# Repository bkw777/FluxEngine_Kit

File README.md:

# FluxEngine Kit

THESE PCBs ARE NOT TESTED YET

This is a set of adapter PCBs and printable snap covers to build a nice version of [FluxEngine](http://cowlark.com/fluxengine/)

I am not the creator of FluxEngine itself, just this adapter PCB and printable cover.

Most people probably do not need any of these pcbs. They are really just to provide convenient support for 8-inch drives.

If you're not trying to use 8-inch drives, then you don't need any adapter pcb like this.  
The FluxEngine pinout is already designed so that you can just solder a 34-pin connector directly to the CY8CKIT-059 fpga board.  
You can use the BOM link below and delete everything but the CY8CKIT-059 and the 34-pin connector, no pcb, no printed cover.

The PCBs are designed to NOT need to be soldered. You can connect and remove and reconnect the fpga board without, and without needing to install actual sockets.
You CAN still solder them normally if you want to make a permanent FluxEngine, you just don't have to.

It means you can swap the same fpga board between all 3 (so far) hat versions, and then still also use the fpga board on a breadboard when not using it for FluxEngine.

What you do is solder pins to the bottom of the fpga board the same as if you were using it on a breadboard. And that's it. You can install actual matching sockets on the hat PCBs, but you don't have to. The zig/zag pin row layout on the hat PCBs makes solid electrical contact with the pins without needing a socket.

For the sake of the solderless pin connections, I suggest getting the PCBs made with ENIG finish (gold plating on the copper).  
It's not required though. Honestly the way the square edges of the pins bite into the via walls it probably will never make any difference.  
Some fabricators charge more than others for ENIG. OSHPark is always ENIG no matter what, so that's easy. But between PCBWAY, JLCPCB, and Elecrow, Elecrow charges a lot less for ENIG.

The cover (both styles) prints easily with any basic home FDM printer with PLA. I actually use a $150 Monoprice from 6 years ago.  

But also these days most of the PCB shops also offer 3d printing, so you can get the pcb and the cover printed professionally in sintered nylon from the same place on the same order.  
The link below is to PCBWAY only because it's the most convenient where you can just click "buy" on something already pre-loaded, but actually if you go to Elecrow and just upload the gerber zip and cover stl, it's just as simple and significantly cheaper, especially with ENIG.

## Parts
[BOM from DigiKey](https://www.digikey.com/short/q5zh79n9)  
[PCB and Cover from PCBWAY](https://www.pcbway.com/project/shareproject/FluxEngine_Hat_e3000eb5.html)

Power supply and cables:  
[Molex power supply](https://amazon.com/dp/B000MGG6SC)  
[Molex to Berg splitter](https://amazon.com/dp/B0002J1KW6)  
[Molex to Molex splitter](https://amazon.com/dp/B00007JO36)  
[Floppy drive cable](https://amazon.com/dp/B07KDJTMGP)  

## Cover

There are a few versions of printable cover in releases, all generated from the same OpenSCAD source.  
Two main styles, simple and fancy, in three sizes each, lowprofile, default, and one for if you have full pin sockets installed.  

## Configuration

The jumpers only affect the 50-pin connector for 8-inch drives.  

### DSKCHG / READY
Connects either the /DSKCHG or /READY output from the drive to the /DSKCHG input on the FluxEngine.  

Install jumper on DSKCHG by default.

### INUSE
Connects the /MOTB (motor-B-on) output from the FluxEngine to the /IN-USE aka /DOOR-LOCK input on the drive.

Not connected by default, but stow a jumper on one pin.

### HLD
Connects the /MOTB (motor-B-on) output from the FluxEngine to the /HEAD-LOAD input on the drive.

Not connected by default, but stow a jumper on one pin.

INUSE/HLD is not either-or. You may need either, or neither, or both.

# Control Data / Magnetic Peripherals / Honeywell 8-inch drives

Some CDC 8-inch drives like the 9404 and 9406-4 lines are Shugart compatible, and so for those just use the SA850 hat like any other Shugart interface drive.

Others have compatible signals but different pinouts.

The two tables below come from two CDC manuals covering many similar drive models spanning several years.  
Left: [CDC FDD FSM ('79)](PCB/datasheets/CDC_77834769_Y__FDD_FSM.pdf)  
Right: [CDC 9406 FSM ('82)](PCB/datasheets/CDC_77614903_AM__9406_FSM.pdf)  

There are two hats that cover the most common CDC pinouts.

The "CDC-daisychain" hat supports all the green highlighted models.

The "CDC-standard" hat supports the blue and purple highlighted models.

"standard" is mis-named because what CDC called "standard interface" in the manuals was several different pinouts and interfaces.  
But of the several pinouts they called "standard", 2 are actually the same except for STEP+DIRECTION vs STEP_IN/STEP_OUT, and most models that don't have the "daisychain" interface seem to have one of these two versions of "standard".  
So the '''CDC-standard''' hat includes logic to optionally convert the STEP+DIRECTION signals from the FluxEngine to STEP_IN/STEP_OUT signals for the drive if needed.

For drives that need STEP_IN/STEP_OUT, install the 2 jumpers on STEP_IN and STEP_OUT. (earlier and less common drives)  

For drives that need STEP+DIRECTION, install the 2 jumpers on DIR and STEP. (default, later and more common drives)  

If you don't need the STEP_IN/STEP_OUT option, you don't need to populate C1 or U1 or the jumper pins. Just use solder or wire in place of the STEP & DIR jumpers and leave the U1 and C1 footprints empty.  

NONE OF THESE ARE TESTED YET  

CDC-daisychain BOM:  
Standard BOM, delete the jumpers.  

CDC-standard BOM:  
Standard BOM, add these:  
[screw terminal header](https://www.digikey.com/en/products/detail/phoenix-contact/5452094/5186805)  
[screw terminal plug](https://www.digikey.com/en/products/detail/phoenix-contact/5452178/5187210)  
[74LVC1G19 1to2 decoder](https://www.digikey.com/en/products/detail/nexperia-usa-inc/74LVC1G19GW-125/1231453)  
[C 0.1u 0805](https://www.digikey.com/en/products/detail/kyocera-avx/KGM21NR71E104KT/1116281)  

### More 8-inch info

The AC & DC power connectors were the same on many drives.  
These are the cable-side connector housings and female pins needed to make proper cables to connect to most drives.

3-pin AC power:  
Housing: [AMP/TE 1-480700-0](https://www.digikey.com/en/products/detail/te-connectivity-amp-connectors/1-480700-0/29339)  
Female pins: [AMP/TE 350536-1](https://www.digikey.com/en/products/detail/te-connectivity-amp-connectors/350536-1/287712)

6-pin DC power:  
Housing: [AMP/TE 1-480270-0](https://www.digikey.com/en/products/detail/te-connectivity-amp-connectors/1-480270-0/15668)  
Female pins: [AMP/TE 61117-1](https://www.digikey.com/en/products/detail/te-connectivity-amp-connectors/61117-1/290254)

They do make dual-output power supplies that output both 5v and 24v, but it's actually cheaper to buy seperate supplies.  
A typical drive draws about 1.0A-1.5A from either DC rail while working.  
Here are a couple of supplies just for convenience & reference:  
[5V 3A Meanwell](https://www.digikey.com/en/products/detail/mean-well-usa-inc/RS-15-5/7706168)  
[24V 3.2A Meanwell](https://www.digikey.com/en/products/detail/mean-well-usa-inc/RS-15-5/7706168)

### Probably CDC-specific

The CDC manuals do not say this anywhere, but many drives have a variant of the 50-pin IDC header with two polarity key slots instead of one in the center. The drawings and actual part numbers in the service manuals only show the normal single-notch type.  
A normal IDC plug with polarity key does not fit. Non-polarized plugs fit, but here are a couple of fully polarity-keyed female IDC plugs that fit:  
[Omron XG4M-5031-T](https://www.digikey.com/en/products/detail/omron-electronics-inc-emc-div/XG4M-5031-T/1829402)  
[Hirose HIF3BA-50D-2.54R](https://www.digikey.com/en/products/detail/hirose-electric-co-ltd/HIF3BA-50D-2-54R-63/12758574)

Connector housing & contacts to fit the 7-pin power connection on CDC drives.  
The pins are .156" pitch, and have a .031"x.062" flat blade shape not square.  
The pin and housing series is called "AMPMODU MOD I", and you want specifically the high pressure version of the receptacles for power vs merely signal usage.  
Only the 4 middle pins are connected, so you could uses as little as a 5-position housing, but ideally you still want a housing with all 7 (or more) positions, and receptacles installed for all 6 pins, because the extra 2 pins provide both strain relief and extra retention friction.  
[TE 87159-7 - AMPMODU MOD I receptacle housing, 7-pin, non-locking, keyed](https://mou.sr/4bhcBrf) (cut the key bumps off)  
[TE 102100-2 - AMPMODU MOD I pin receptacle, non-locking high-pressure 18-22awg gold-30uin](https://mou.sr/44tt5K6) (need 6)  
[TE 87116-2 - AMPMODU MOD I keying plug](https://us.rs-online.com/product/te-connectivity/87116-2/70287356/) (need 1)

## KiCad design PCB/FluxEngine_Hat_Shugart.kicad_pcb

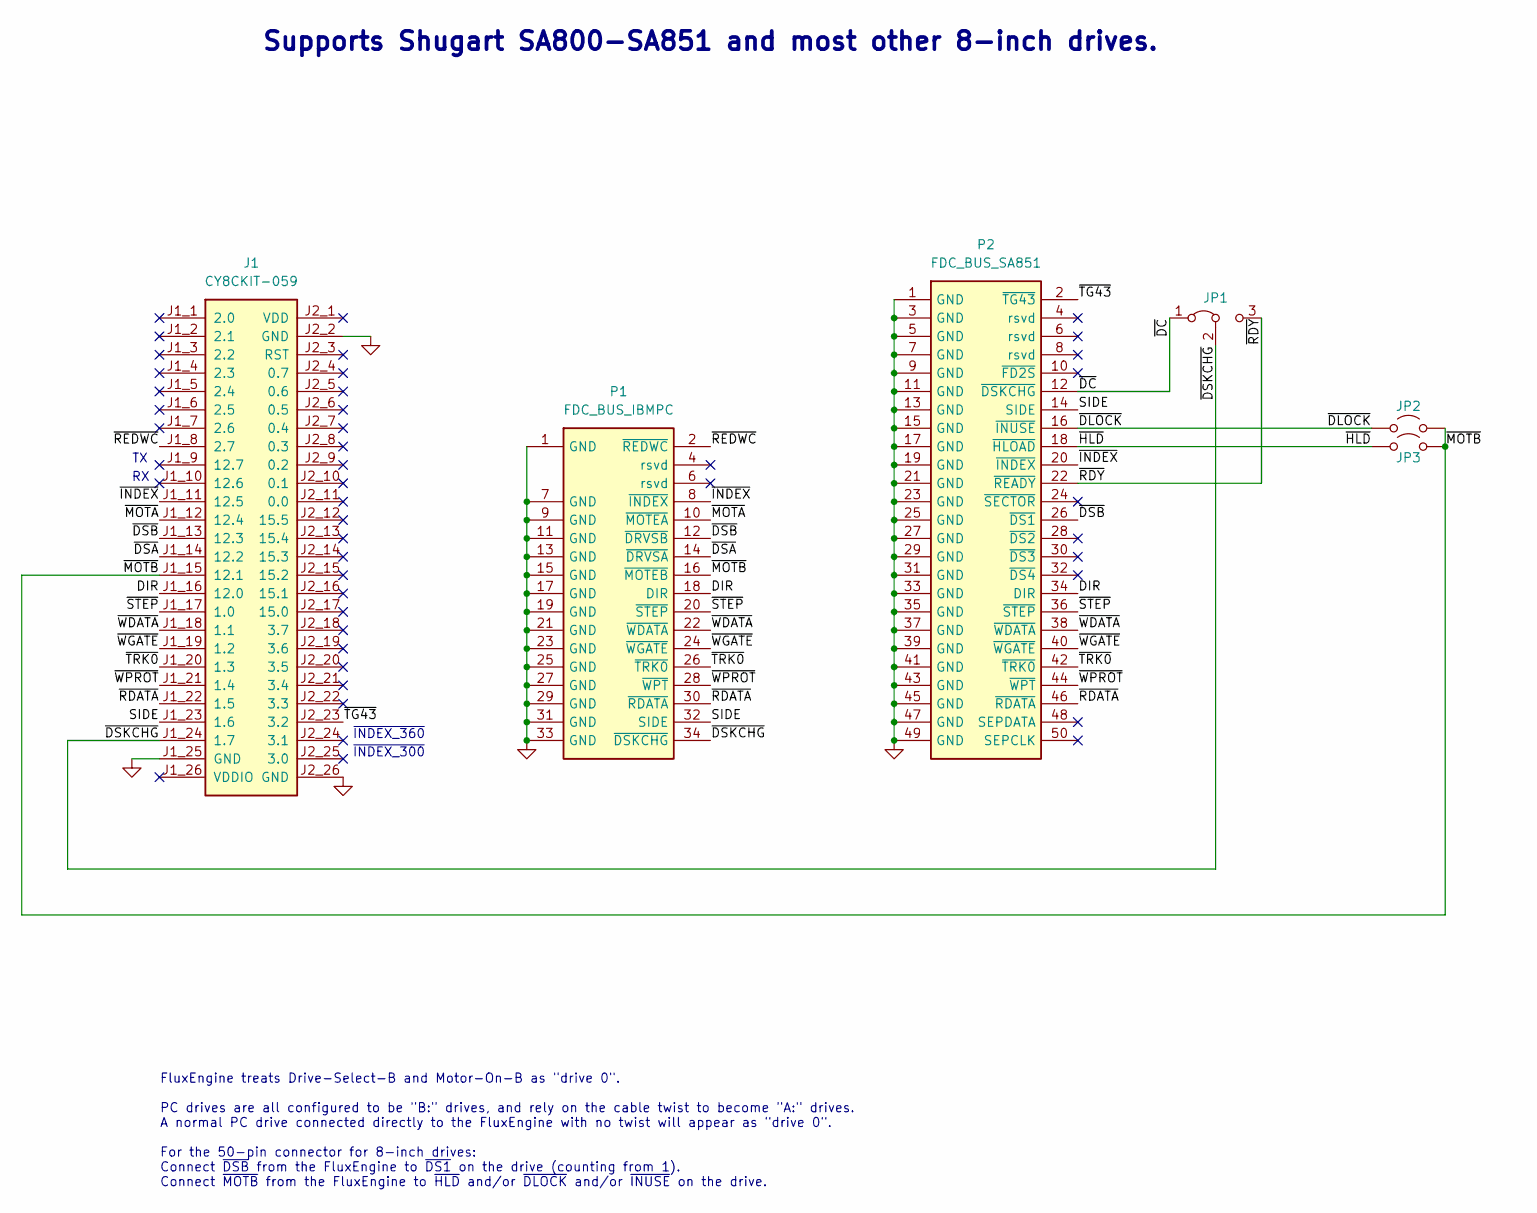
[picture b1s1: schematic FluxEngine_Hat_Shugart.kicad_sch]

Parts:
J1: CY8CKIT-059; CY8CKIT-059 dry fit
JP1: Jumper_3_Bridged12; PinHeader_1x03_P2.54mm_Vertical
JP2, JP3: Jumper_2_Open; PinHeader_1x02_P2.54mm_Vertical
P1: FDC_BUS_IBMPC; IDC-Header_2x17_P2.54mm_Latch_Vertical - FDD
P2: FDC_BUS_SA851; IDC-Header_2x25_P2.54mm_Latch_Vertical

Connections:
/DIR: J1.J1_16 (12.0), P1.18 (DIR), P2.34 (DIR)
/SIDE: J1.J1_23 (1.6), P1.32 (SIDE), P2.14 (SIDE)
/~DC: JP1.1 (A), P2.12 (~DSKCHG)
/~DLOCK: JP2.1 (A), P2.16 (~INUSE)
/~DSA: J1.J1_14 (12.2), P1.14 (~DRVSA)
/~DSB: J1.J1_13 (12.3), P1.12 (~DRVSB), P2.26 (~DS1)
/~DSKCHG: J1.J1_24 (1.7), JP1.2 (C), P1.34 (~DSKCHG)
/~HLD: JP3.1 (A), P2.18 (~HLOAD)
/~INDEX: J1.J1_11 (12.5), P1.8 (~INDEX), P2.20 (~INDEX)
/~MOTA: J1.J1_12 (12.4), P1.10 (~MOTEA)
/~MOTB: J1.J1_15 (12.1), JP2.2 (B), JP3.2 (B), P1.16 (~MOTEB)
/~RDATA: J1.J1_22 (1.5), P1.30 (~RDATA), P2.46 (~RDATA)
/~RDY: JP1.3 (B), P2.22 (~READY)
/~REDWC: J1.J1_8 (2.7), P1.2 (~REDWC)
/~STEP: J1.J1_17 (1.0), P1.20 (~STEP), P2.36 (~STEP)
/~TG43: J1.J2_23 (3.2), P2.2 (~TG43)
/~TRK0: J1.J1_20 (1.3), P1.26 (~TRK0), P2.42 (~TRK0)
/~WDATA: J1.J1_18 (1.1), P1.22 (~WDATA), P2.38 (~WDATA)
/~WGATE: J1.J1_19 (1.2), P1.24 (~WGATE), P2.40 (~WGATE)
/~WPROT: J1.J1_21 (1.4), P1.28 (~WPT), P2.44 (~WPT)
GND: J1.J1_25 (GND), J1.J2_2 (GND), J1.J2_26 (GND), P1.1 (GND), P1.7 (GND), P1.9 (GND), P1.11 (GND), P1.13 (GND), P1.15 (GND), P1.17 (GND), P1.19 (GND), P1.21 (GND), P1.23 (GND), P1.25 (GND), P1.27 (GND), P1.29 (GND), P1.31 (GND), P1.33 (GND), P2.1 (GND), P2.3 (GND), P2.5 (GND), P2.7 (GND), P2.9 (GND), P2.11 (GND), P2.13 (GND), P2.15 (GND), P2.17 (GND), P2.19 (GND), P2.21 (GND), P2.23 (GND), P2.25 (GND), P2.27 (GND), P2.29 (GND), P2.31 (GND), P2.33 (GND), P2.35 (GND), P2.37 (GND), P2.39 (GND), P2.41 (GND), P2.43 (GND), P2.45 (GND), P2.47 (GND), P2.49 (GND)

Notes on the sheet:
~{INDEX_300}
FluxEngine treats Drive-Select-B and Motor-On-B as "drive 0". PC drives are all configured to be "B:" drives, and rely on the cable twist to become "A:" drives. A normal PC drive connected directly to the FluxEngine with no twist will appear as "drive 0". For the 50-pin connector for 8-inch drives: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
Supports Shugart SA800-SA851 and most other 8-inch drives.
~{INDEX_360}

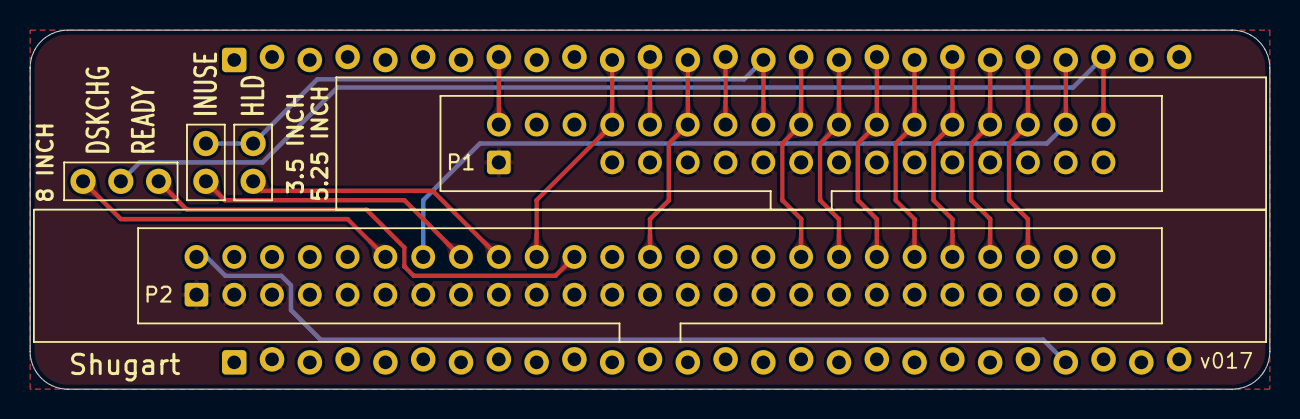
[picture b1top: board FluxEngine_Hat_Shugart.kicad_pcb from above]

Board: 2 copper layers, 83.3 x 24.1 mm, 6 parts (1 on the bottom side), 21 nets.

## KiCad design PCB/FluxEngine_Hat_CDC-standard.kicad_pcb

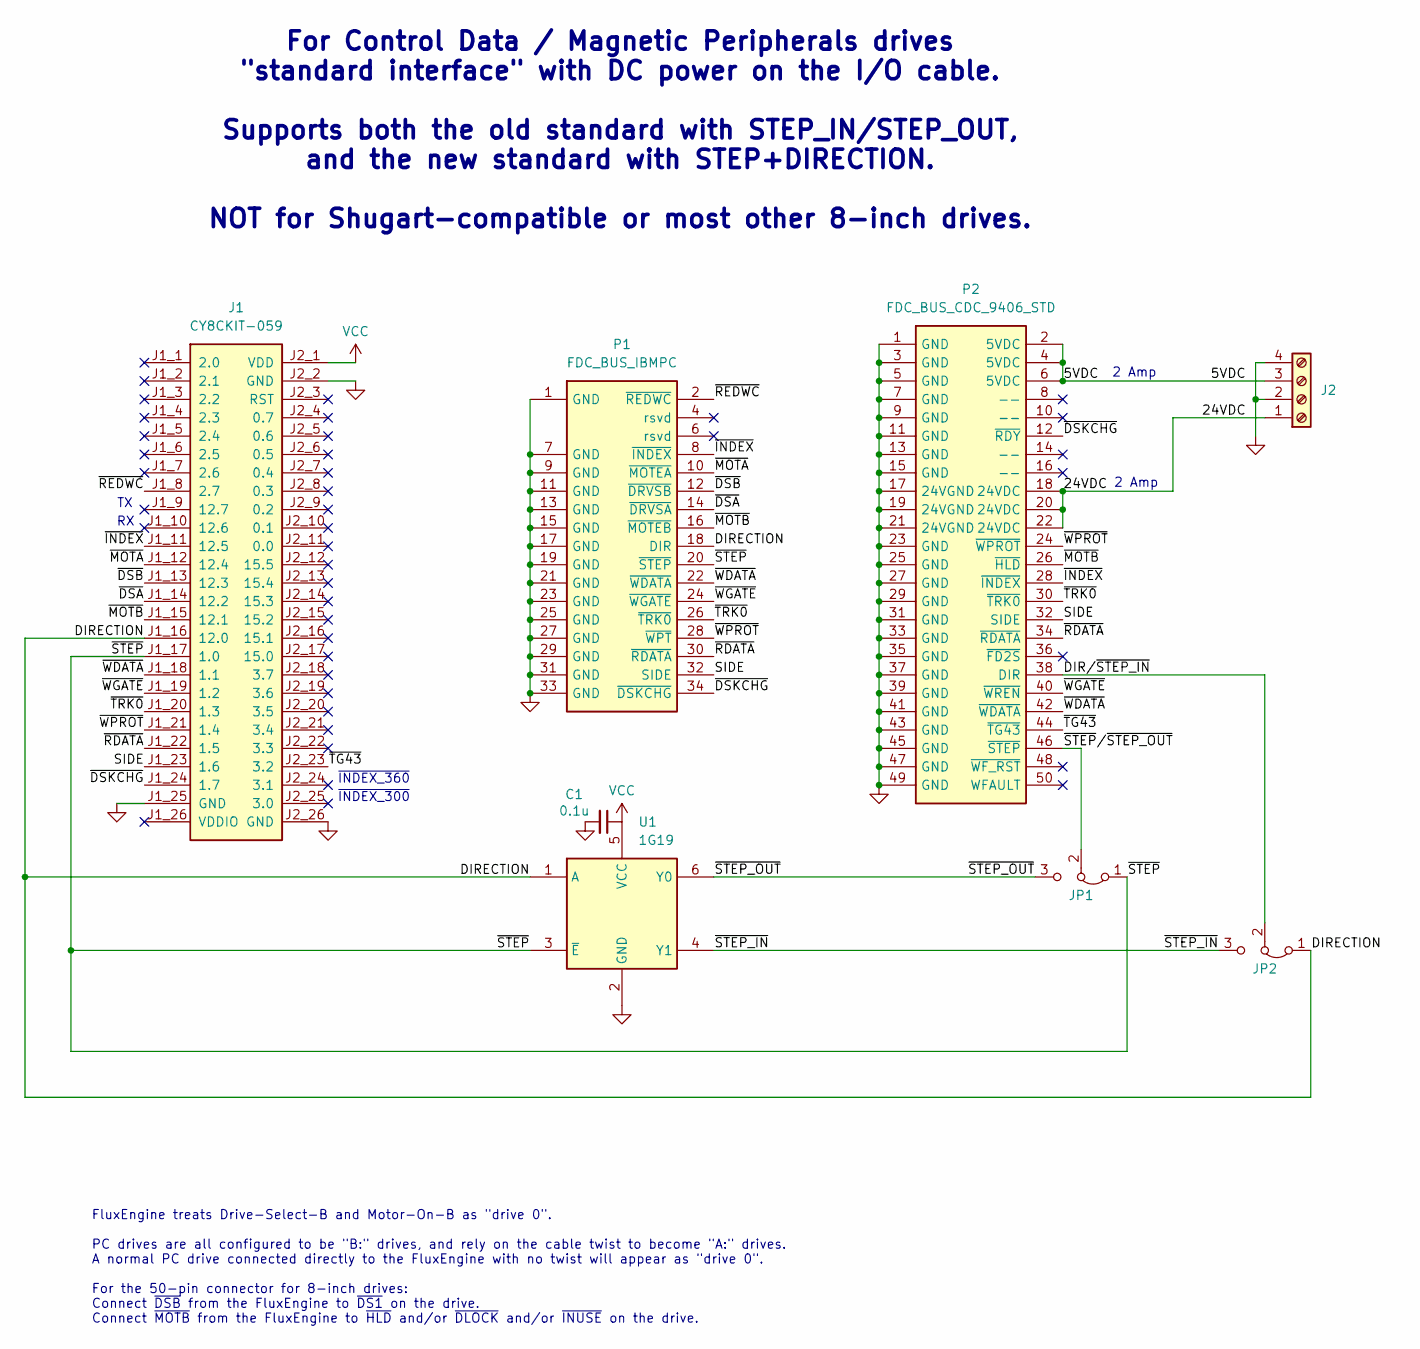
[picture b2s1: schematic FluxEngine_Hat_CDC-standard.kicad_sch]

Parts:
C1: 0.1u; C_0805_2012Metric
J1: CY8CKIT-059; CY8CKIT-059 dry fit
J2: Screw_Terminal_01x04; ScrewTerminal_1x04_P3.5mm_vertical
JP1, JP2: Jumper_3_Bridged12; PinHeader_1x03_P2.54mm_Vertical
P1: FDC_BUS_IBMPC; IDC-Header_2x17_P2.54mm_Latch_Vertical - FDD
P2: FDC_BUS_CDC_9406_STD; IDC-Header_2x25_P2.54mm_Latch_Vertical
U1: 1G19; SOT-363_SC-70-6

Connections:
/5VDC: J2.3, P2.2 (5VDC), P2.4 (5VDC), P2.6 (5VDC)
/24VDC: J2.1, P2.18 (24VDC), P2.20 (24VDC), P2.22 (24VDC)
/DIRECTION: J1.J1_16 (12.0), JP2.1 (A), P1.18 (DIR), U1.1 (A)
/DIR/~STEP_IN: JP2.2 (C), P2.38 (DIR)
/SIDE: J1.J1_23 (1.6), P1.32 (SIDE), P2.32 (SIDE)
/~DSA: J1.J1_14 (12.2), P1.14 (~DRVSA)
/~DSB: J1.J1_13 (12.3), P1.12 (~DRVSB)
/~DSKCHG: J1.J1_24 (1.7), P1.34 (~DSKCHG), P2.12 (~RDY)
/~INDEX: J1.J1_11 (12.5), P1.8 (~INDEX), P2.28 (~INDEX)
/~MOTA: J1.J1_12 (12.4), P1.10 (~MOTEA)
/~MOTB: J1.J1_15 (12.1), P1.16 (~MOTEB), P2.26 (~HLD)
/~RDATA: J1.J1_22 (1.5), P1.30 (~RDATA), P2.34 (~RDATA)
/~REDWC: J1.J1_8 (2.7), P1.2 (~REDWC)
/~STEP_IN: JP2.3 (B), U1.4 (Y1)
/~STEP_OUT: JP1.3 (B), U1.6 (Y0)
/~STEP: J1.J1_17 (1.0), JP1.1 (A), P1.20 (~STEP), U1.3 (~E)
/~STEP/~STEP_OUT: JP1.2 (C), P2.46 (~STEP)
/~TG43: J1.J2_23 (3.2), P2.44 (~TG43)
/~TRK0: J1.J1_20 (1.3), P1.26 (~TRK0), P2.30 (~TRK0)
/~WDATA: J1.J1_18 (1.1), P1.22 (~WDATA), P2.42 (~WDATA)
/~WGATE: J1.J1_19 (1.2), P1.24 (~WGATE), P2.40 (~WREN)
/~WPROT: J1.J1_21 (1.4), P1.28 (~WPT), P2.24 (~WPROT)
GND: C1.2, J1.J1_25 (GND), J1.J2_2 (GND), J1.J2_26 (GND), J2.2, J2.4, P1.1 (GND), P1.7 (GND), P1.9 (GND), P1.11 (GND), P1.13 (GND), P1.15 (GND), P1.17 (GND), P1.19 (GND), P1.21 (GND), P1.23 (GND), P1.25 (GND), P1.27 (GND), P1.29 (GND), P1.31 (GND), P1.33 (GND), P2.1 (GND), P2.3 (GND), P2.5 (GND), P2.7 (GND), P2.9 (GND), P2.11 (GND), P2.13 (GND), P2.15 (GND), P2.17 (24VGND), P2.19 (24VGND), P2.21 (24VGND), P2.23 (GND), P2.25 (GND), P2.27 (GND), P2.29 (GND), P2.31 (GND), P2.33 (GND), P2.35 (GND), P2.37 (GND), P2.39 (GND), P2.41 (GND), P2.43 (GND), P2.45 (GND), P2.47 (GND), P2.49 (GND), U1.2 (GND)
VCC: C1.1, J1.J2_1 (VDD), U1.5 (VCC)

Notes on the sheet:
FluxEngine treats Drive-Select-B and Motor-On-B as "drive 0". PC drives are all configured to be "B:" drives, and rely on the cable twist to become "A:" drives. A normal PC drive connected directly to the FluxEngine with no twist will appear as "drive 0". For the 50-pin connector for 8-inch drives: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
~{INDEX_300}
For Control Data / Magnetic Peripherals drives "standard interface" with DC power on the I/O cable. Supports both the old standard with STEP_IN/STEP_OUT, and the new standard with STEP+DIRECTION. NOT for Shugart-compatible or most other 8-inch drives.
2 Amp
~{INDEX_360}

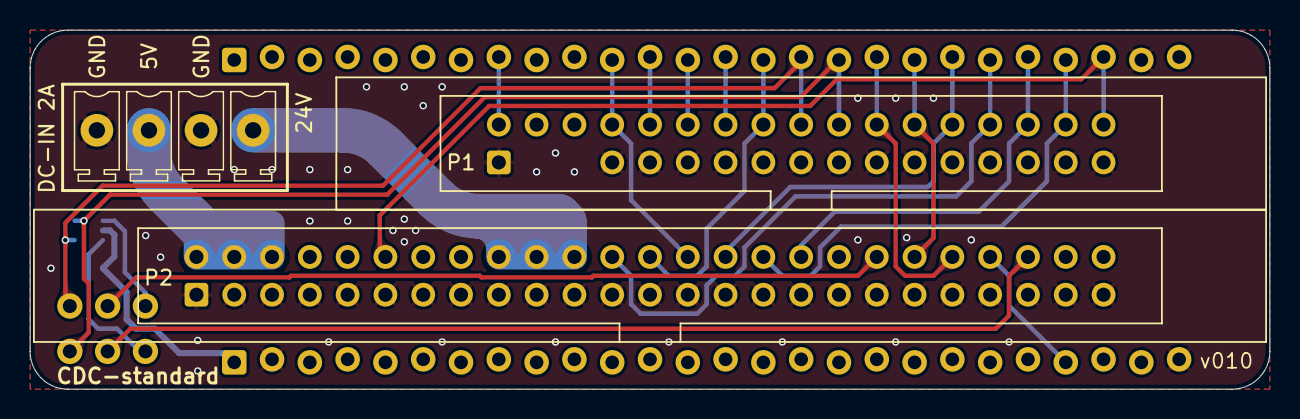
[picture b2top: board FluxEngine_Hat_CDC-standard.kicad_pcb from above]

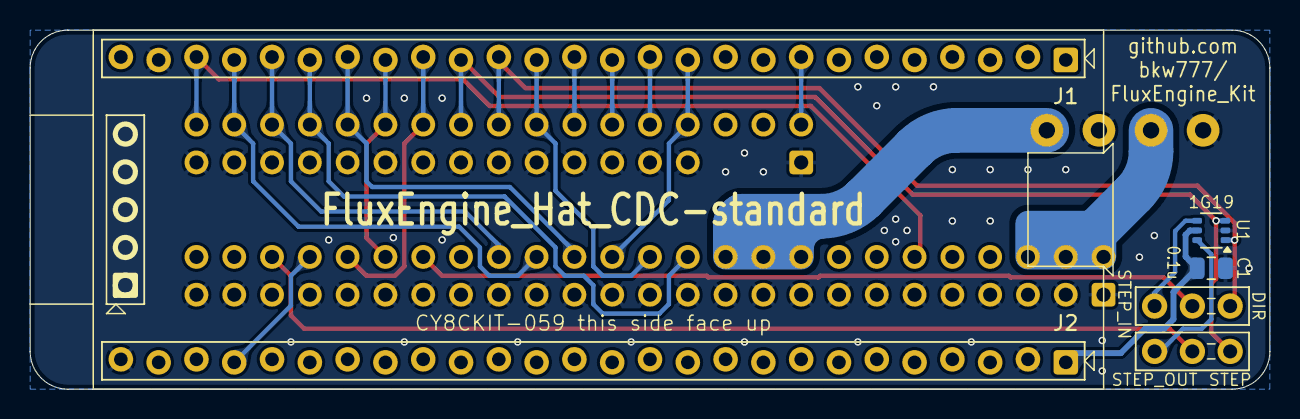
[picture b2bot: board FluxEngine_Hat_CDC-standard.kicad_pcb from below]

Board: 2 copper layers, 83.3 x 24.1 mm, 8 parts (5 on the bottom side), 24 nets.

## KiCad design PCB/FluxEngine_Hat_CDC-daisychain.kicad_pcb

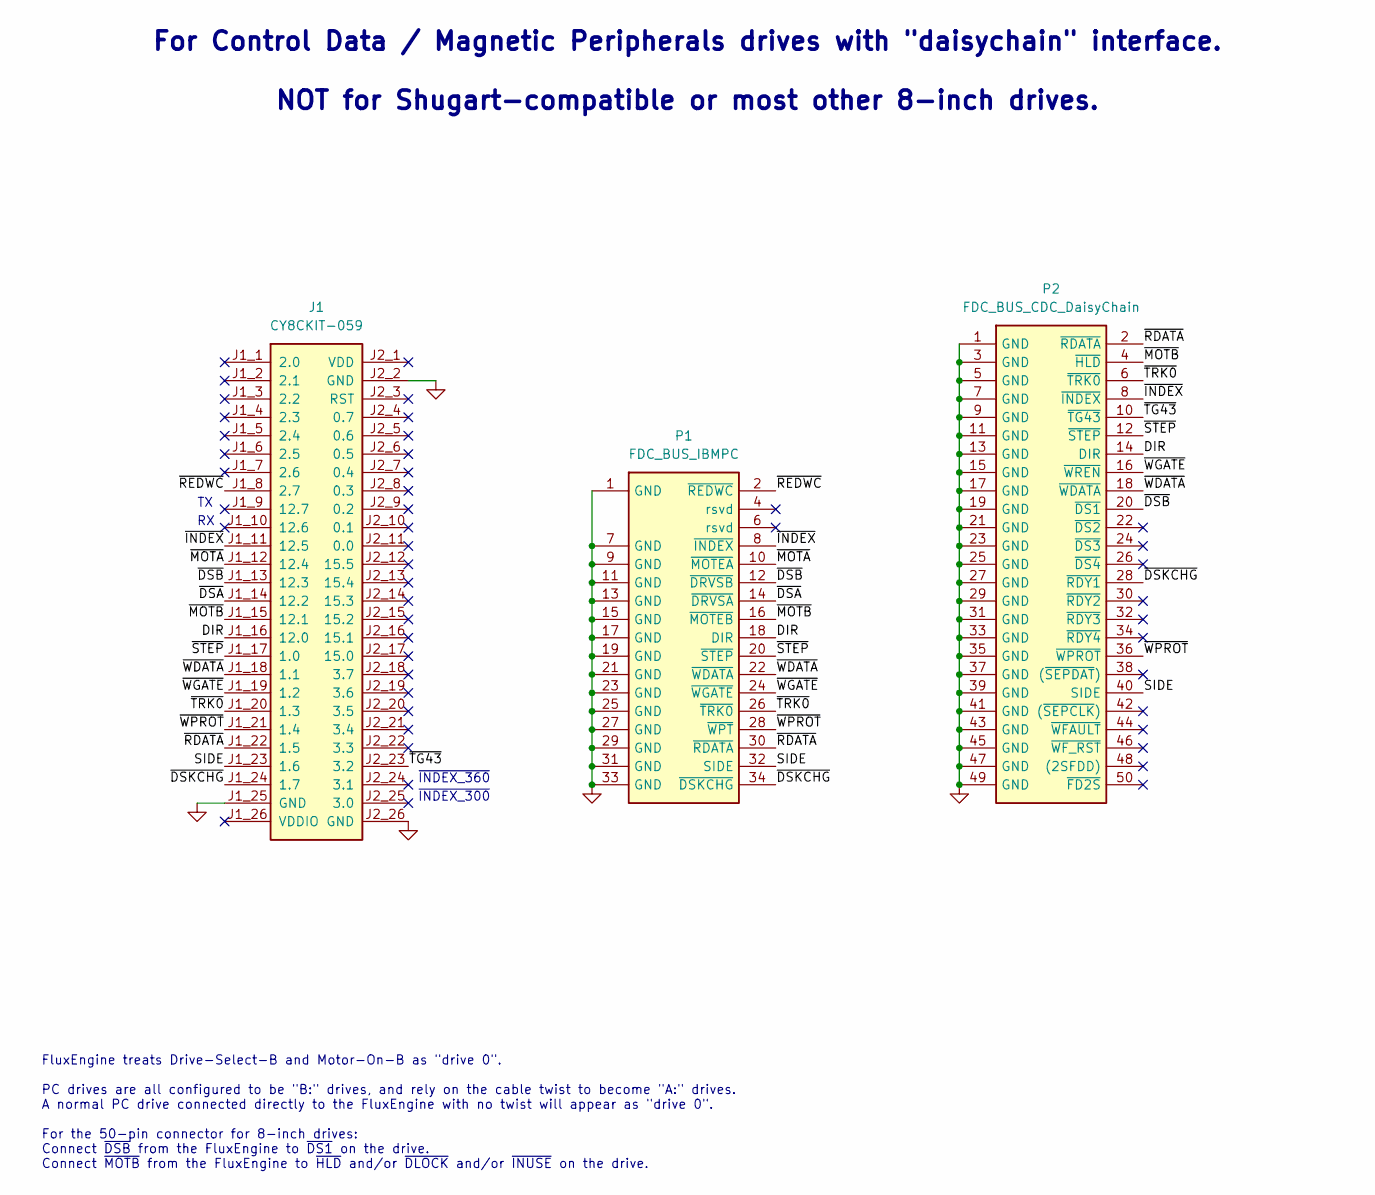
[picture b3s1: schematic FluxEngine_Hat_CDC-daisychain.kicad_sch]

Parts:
J1: CY8CKIT-059; CY8CKIT-059 dry fit
P1: FDC_BUS_IBMPC; IDC-Header_2x17_P2.54mm_Latch_Vertical - FDD
P2: FDC_BUS_CDC_DaisyChain; IDC-Header_2x25_P2.54mm_Latch_Vertical

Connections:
/DIR: J1.J1_16 (12.0), P1.18 (DIR), P2.14 (DIR)
/SIDE: J1.J1_23 (1.6), P1.32 (SIDE), P2.40 (SIDE)
/~DSA: J1.J1_14 (12.2), P1.14 (~DRVSA)
/~DSB: J1.J1_13 (12.3), P1.12 (~DRVSB), P2.20 (~DS1)
/~DSKCHG: J1.J1_24 (1.7), P1.34 (~DSKCHG), P2.28 (~RDY1)
/~INDEX: J1.J1_11 (12.5), P1.8 (~INDEX), P2.8 (~INDEX)
/~MOTA: J1.J1_12 (12.4), P1.10 (~MOTEA)
/~MOTB: J1.J1_15 (12.1), P1.16 (~MOTEB), P2.4 (~HLD)
/~RDATA: J1.J1_22 (1.5), P1.30 (~RDATA), P2.2 (~RDATA)
/~REDWC: J1.J1_8 (2.7), P1.2 (~REDWC)
/~STEP: J1.J1_17 (1.0), P1.20 (~STEP), P2.12 (~STEP)
/~TG43: J1.J2_23 (3.2), P2.10 (~TG43)
/~TRK0: J1.J1_20 (1.3), P1.26 (~TRK0), P2.6 (~TRK0)
/~WDATA: J1.J1_18 (1.1), P1.22 (~WDATA), P2.18 (~WDATA)
/~WGATE: J1.J1_19 (1.2), P1.24 (~WGATE), P2.16 (~WREN)
/~WPROT: J1.J1_21 (1.4), P1.28 (~WPT), P2.36 (~WPROT)
GND: J1.J1_25 (GND), J1.J2_2 (GND), J1.J2_26 (GND), P1.1 (GND), P1.7 (GND), P1.9 (GND), P1.11 (GND), P1.13 (GND), P1.15 (GND), P1.17 (GND), P1.19 (GND), P1.21 (GND), P1.23 (GND), P1.25 (GND), P1.27 (GND), P1.29 (GND), P1.31 (GND), P1.33 (GND), P2.1 (GND), P2.3 (GND), P2.5 (GND), P2.7 (GND), P2.9 (GND), P2.11 (GND), P2.13 (GND), P2.15 (GND), P2.17 (GND), P2.19 (GND), P2.21 (GND), P2.23 (GND), P2.25 (GND), P2.27 (GND), P2.29 (GND), P2.31 (GND), P2.33 (GND), P2.35 (GND), P2.37 (GND), P2.39 (GND), P2.41 (GND), P2.43 (GND), P2.45 (GND), P2.47 (GND), P2.49 (GND)

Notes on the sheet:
~{INDEX_300}
~{INDEX_360}
For Control Data / Magnetic Peripherals drives with "daisychain" interface. NOT for Shugart-compatible or most other 8-inch drives.
FluxEngine treats Drive-Select-B and Motor-On-B as "drive 0". PC drives are all configured to be "B:" drives, and rely on the cable twist to become "A:" drives. A normal PC drive connected directly to the FluxEngine with no twist will appear as "drive 0". For the 50-pin connector for 8-inch drives: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

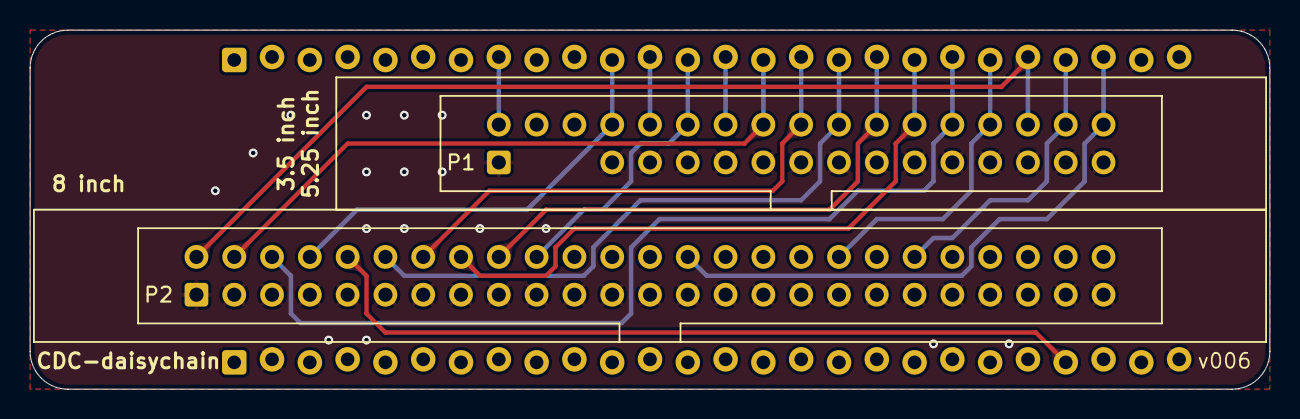
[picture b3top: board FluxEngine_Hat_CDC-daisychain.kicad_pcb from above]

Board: 2 copper layers, 83.3 x 24.1 mm, 3 parts (1 on the bottom side), 17 nets.

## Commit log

2024-04-09 initial
2024-04-10 fdd symbols, rename to _Hat
2024-04-10 readme
2024-04-13 v003 flip fpga board over
2024-04-16 jumper options and printable case
2024-04-17 snap cover, better 3d model files
2024-04-17 clean up unused symbols, footprints, models
2024-04-19 filenames vs readme
2024-04-19 refactor cover, add slim cover variant
2024-04-20 fix posts in cover not touching outer wall
2024-04-20 slight adjustments to the cover
2024-04-21 better jumper arrangement, fix some signal names
2024-04-21 silkscreen & pics
2024-04-22 add FluxEngine_SlipCover.FCStd
2024-04-22 slipcover
2024-04-22 enclosures
2024-04-22 pics
2024-04-23 solderless pins footprint, add simple cover for solderless and sockets
2024-04-24 CDC/MPI manual
2024-04-25 add CDC9406 type 1 & 2
2024-04-25 CDC pinouts
2024-04-25 readme & remove slash from page names
2024-04-27 cdc convert step
2024-04-27 WIP add step convert
2024-04-30 more CDC work
2024-04-30 Combined CDC new & old standard interface
2024-05-01 reamde typo
2024-05-02 rename some of the printable covers
2024-05-02 all covers from openscad
2024-05-02 remove stl outputs from repo
2024-05-03 cover scad refactor some
2024-05-03 increase fitment clearance in simple cover
2024-05-04 schematic notes
2024-05-06 silkscreen, pics
2024-05-06 readme, pics
2024-05-11 fix CDC-standard backwards step_in/step_out decoding
2024-05-11 CDC-standard silkscreen
2024-05-11 CDC-standard adjust a trace
2024-05-25 reduce thermal spoke width
2024-05-28 rotate 1G19 for easier hand soldering
2024-06-06 CDC-standard traces to U1
2024-08-08 staggered rows offset & direction
2024-08-08 shugart silkscreen

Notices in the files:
PCB/FluxEngine_Hat_CDC-daisychain.kicad_sch:
CC BY-SA
